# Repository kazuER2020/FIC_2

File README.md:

# FIC_2
# 片手入力デバイス

**9個のタクトスイッチ**と**1個のロータリーエンコーダ**から構成される、コンパクトな片手用入力デバイスです。  
USB経由でPCと接続し、事前に設定されたキーボードショートカットを送信することで、**マクロ実行や作業効率化**に活用できます。

## 🔧 主な機能

- **9個のタクトスイッチ + 1個のロータリーエンコーダ**
- **USB HID対応（Atmega32u4マイコンを使用）**  
  PCに接続すると、標準のUSBキーボードとして認識されます。
- **任意のキー操作を割り当て可能**  
  各スイッチやエンコーダの回転動作にキーボードコマンドを自由に設定可能です。
- **最大3レイヤ対応（合計27通りのキーマッピング）**  
  用途に応じてレイヤを切り替え、多機能な操作を実現できます。

## 🖥️ 使用方法

1. デバイスをUSBケーブルでPCに接続します。
2. ドライバ不要で、自動的にキーボードデバイスとして認識されます。
3. スイッチの操作やエンコーダの回転により、あらかじめ設定したショートカットキーが送信されます。
4. レイヤ切り替え用のボタンやエンコーダ操作により、3種類のキーレイアウトを使い分け可能です。

## ✏️ カスタムキー設定方法

カスタムキーの設定は、**Arduino IDE** を使用してファームウェアを直接書き換えることで行います。  
キーの割り当てやレイヤの定義は、以下のスケッチファイル内に記述されています。

- `Arduino/key_main/key_main.ino` をご参照ください。
  
## 🔲 ブロック図

キー割り当てやレイヤ構成の**ブロック図**は以下のファイルを参照してください。

- [`PCB/BrockDiagram/FIC2.drawio.pdf`](./PCB/BrockDiagram/FIC2.drawio.pdf)

## 📐 回路図

上記ブロック図をもとに、**KiCad 5.1.2** にて作成した回路図は以下の通りです。

- [`PCB/FIC_2/FIC_2.pdf`](./PCB/FIC_2/FIC_2.pdf)

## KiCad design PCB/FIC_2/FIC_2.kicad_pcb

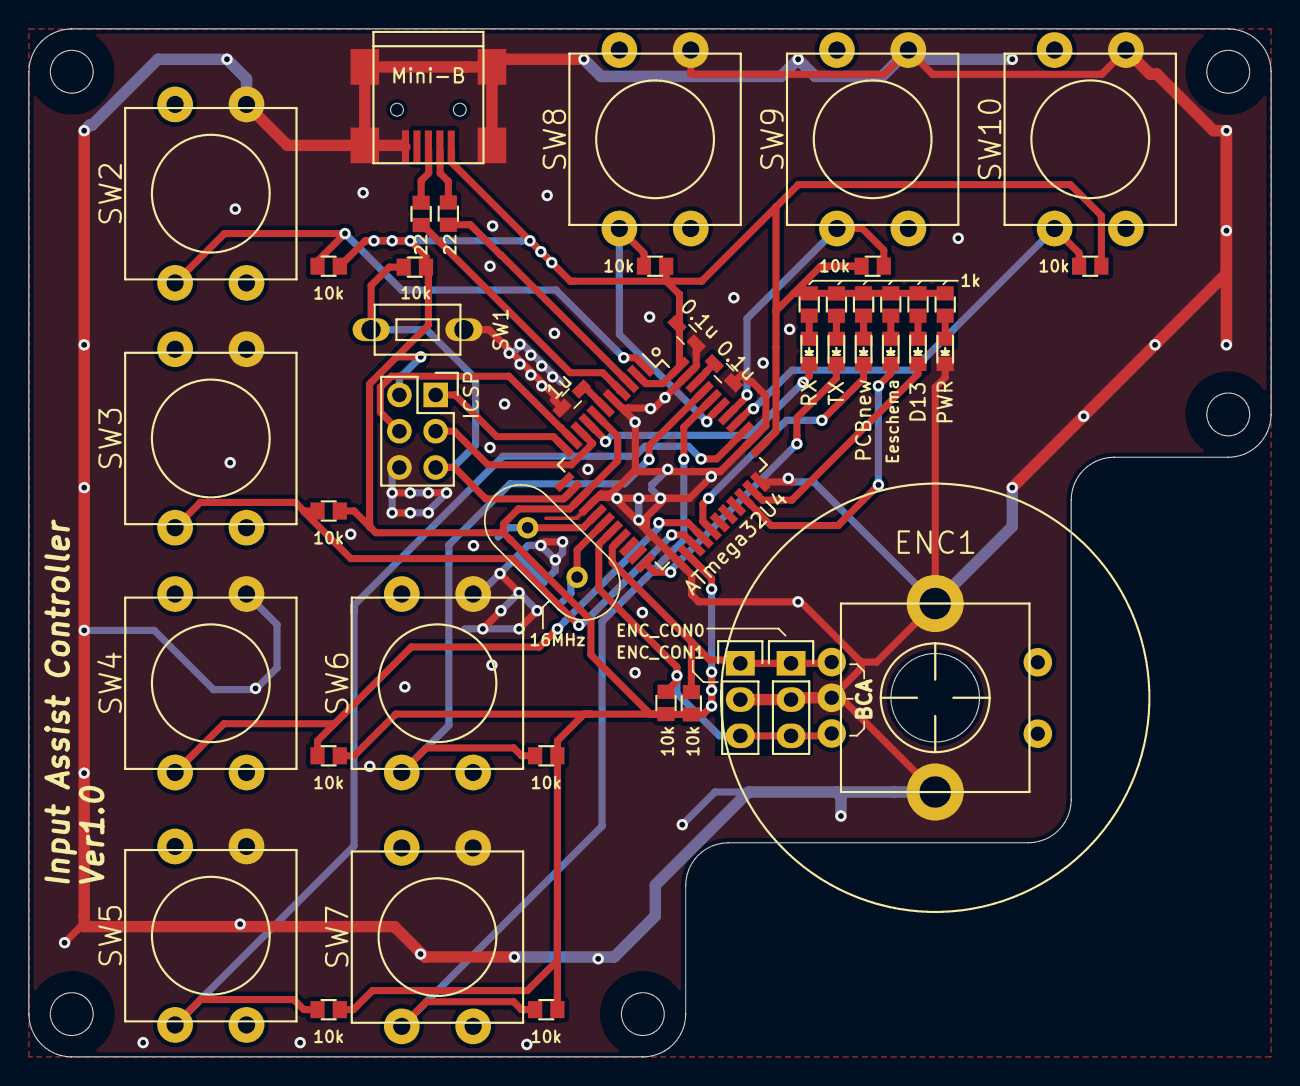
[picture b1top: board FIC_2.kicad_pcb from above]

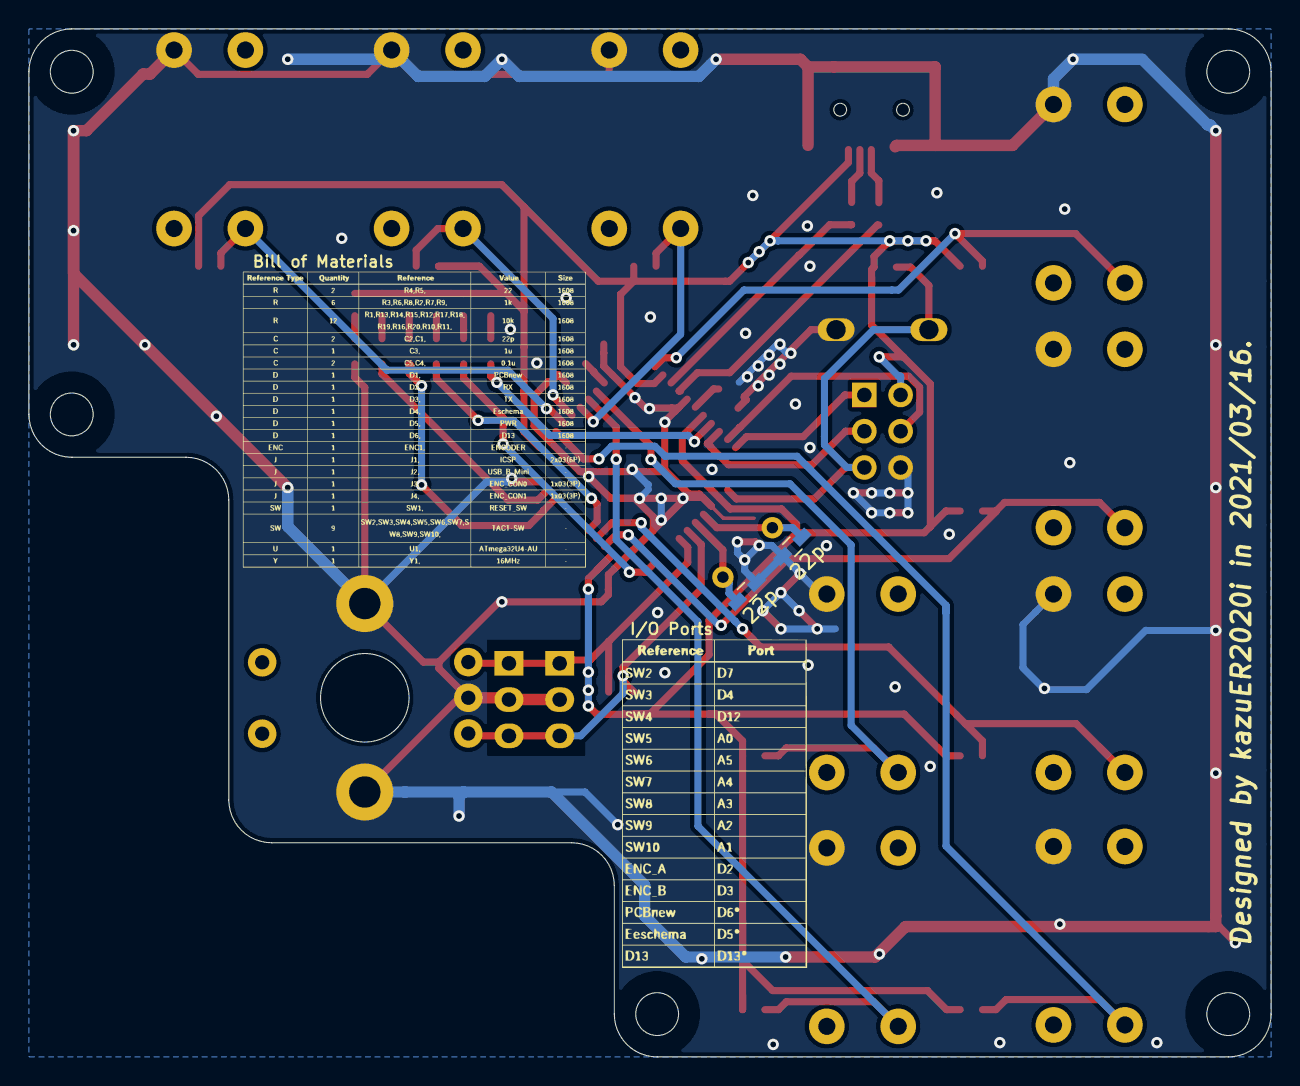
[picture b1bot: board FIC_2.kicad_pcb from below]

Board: 2 copper layers, 87.0 x 72.0 mm, 48 parts (2 on the bottom side), 36 nets.

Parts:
0.1u, 0.1u#2: 0.1u; C_0603_HandSoldering
1u: 1u; C_0603_HandSoldering
16MHz: 16MHz; Crystal_HC18-U_Vertical
22p, 22p#2: 22p; C_0603_HandSoldering
ATmega32U4: ATmega32U4-AU; IC_TQFP-044_10x10mm_Pitch0.8mm
D1: PCBnew; LED_0603
D2: RX; LED_0603
D3: TX; LED_0603
D4: Eeschema; LED_0603
D5: PWR; LED_0603
D6: D13; LED_0603
ENC1: ENCODER; ENCODER-PEC12R
ENC_CON0: ENC_CON0; X_Pin_Header_Straight_1x03
ENC_CON1: ENC_CON1; X_Pin_Header_Straight_1x03
ICSP: ICSP; X_Socket_Strip_Straight_2x03
Mini-B: USB_B_Mini; USB_Mini-B
R1, R10, R11, R12, R13, R14, R15, R16, R17, R18, R19, R20: 10k; R_0603
R2, R3, R6, R7, R8, R9: 1k; R_0603
R4, R5: 22; R_0603
SW1: RESET_SW; TVBP06-B043CW-B
SW2, SW3, SW4, SW5, SW6, SW7, SW8, SW9, SW10: TACT-SW; AKIZUKI-TACT

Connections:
+5V: 0.1u.2, ATmega32U4.2, ATmega32U4.7, ATmega32U4.14, ATmega32U4.24, ATmega32U4.34, ATmega32U4.44, ICSP.2, Mini-B.1, R1.1, R2.2, R3.2, R6.2, R7.2, R8.2, R9.2, R10.2, R11.2, R12.2, R13.2, R14.2, R15.2, R16.2, R17.2, R18.2, R19.2, R20.2
/A0: ATmega32U4.36, R15.1, SW5.1
/A1: ATmega32U4.37, R20.1, SW10.1
/A2: ATmega32U4.38, R19.1, SW9.1
/A3: ATmega32U4.39, R18.1, SW8.1
/A4: ATmega32U4.40, R17.1, SW7.1
/A5: ATmega32U4.41, R16.1, SW6.1
/D2: ATmega32U4.19, ENC1.1, ENC_CON0.1, ENC_CON1.1, R11.1
/D3: ATmega32U4.18, ENC1.3, ENC_CON0.3, ENC_CON1.3, R10.1
/D4: ATmega32U4.25, R13.1, SW3.1
/D5*: ATmega32U4.31, D4.1
/D6*: ATmega32U4.27, D1.1
/D7: ATmega32U4.1, R12.1, SW2.1
/D12: ATmega32U4.26, R14.1, SW4.1
/D13*: ATmega32U4.32, D6.1
/MISO: ATmega32U4.11, ICSP.1
/MOSI: ATmega32U4.10, ICSP.4
/RXLED: ATmega32U4.8, D2.1
/SCK: ATmega32U4.9, ICSP.3
/TXLED: ATmega32U4.22, D3.1
/~RESET: ATmega32U4.13, ICSP.5, R1.2, SW1.1
GND: 0.1u.1, 0.1u#2.2, 1u.1, 22p.1, 22p#2.1, ATmega32U4.5, ATmega32U4.15, ATmega32U4.23, ATmega32U4.33, ATmega32U4.35, ATmega32U4.43, D5.1, ENC1.2, ENC1.6, ENC1.7, ENC_CON0.2, ENC_CON1.2, ICSP.6, Mini-B.5, Mini-B.6, SW1.2, SW2.4, SW3.4, SW4.4, SW5.4, SW6.4, SW7.4, SW8.4, SW9.4, SW10.4
unnamed: 16MHz.1, 22p.2, ATmega32U4.17
unnamed: 16MHz.2, 22p#2.2, ATmega32U4.16
unnamed: 1u.2, ATmega32U4.6
unnamed: 0.1u#2.1, ATmega32U4.42
unnamed: D1.2, R2.1
unnamed: D2.2, R3.1
unnamed: D3.2, R6.1
unnamed: D4.2, R7.1
unnamed: D5.2, R8.1
unnamed: D6.2, R9.1
unnamed: Mini-B.2, R5.2
unnamed: Mini-B.3, R4.2
unnamed: ATmega32U4.4, R4.1
unnamed: ATmega32U4.3, R5.1
